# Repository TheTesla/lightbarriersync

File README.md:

# Light Barrier Synchronous

This is a robust continuous wave modulated light barrier with a synchronous detector. The sensitivity is very low against other modulated ligth sources. All electrical interfaces are protected against reverse polarity, over voltage and over current.

It contains only easily available discrete standard components and the board has only one solder side.

## Technical Data

| Parameter              | Min | Typ | Max | Unit |
| ---------------------- | --- | --- | --- | ---- |
| Operating Voltage      | 3.3 | 5   |  35 |    V |
| Current Consumption    |     |     |  10 |   mA |
| Output Sink Current    |     |     | 800 |   uA |
| Temperature Range      | 0   |     |  70 |   °C |
| Carrier Frequency      |     | 7   |     |  kHz |

## Pictures

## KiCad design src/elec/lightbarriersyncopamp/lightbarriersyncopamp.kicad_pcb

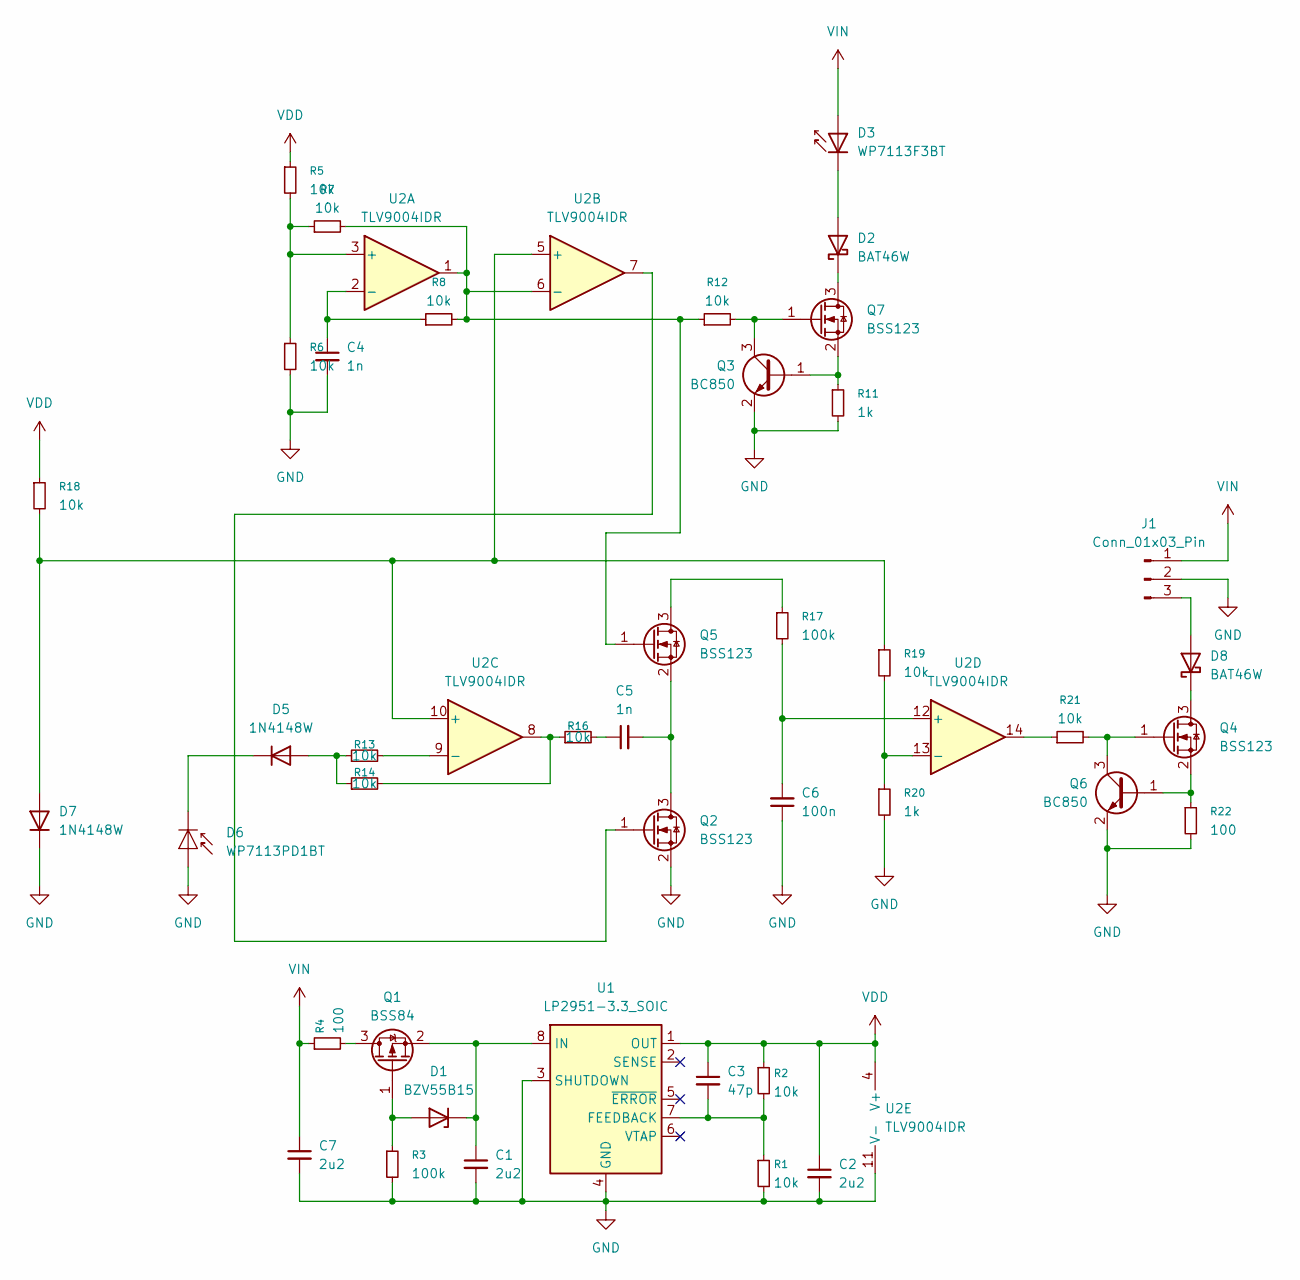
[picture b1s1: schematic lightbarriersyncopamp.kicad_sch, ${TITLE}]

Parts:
C1, C2, C7: 2u2; C_0805_2012Metric
C3: 47p; C_0805_2012Metric
C4, C5: 1n; C_0805_2012Metric
C6: 100n; C_0805_2012Metric
D1: BZV55B15; D_MiniMELF
D2, D8: BAT46W; D_SOD-123
D3: WP7113F3BT; LED_D5.0mm_IRGrey
D5, D7: 1N4148W; D_SOD-123
D6: WP7113PD1BT; LED_D5.0mm_IRGrey
J1: Conn_01x03_Pin; PinHeader_1x03_P2.54mm_Vertical
Q1: BSS84; SOT-23
Q2, Q4, Q5, Q7: BSS123; SOT-23
Q3, Q6: BC850; SOT-23
R1, R2, R5, R6, R7, R8, R12, R13, R14, R16, R18, R19, R21: 10k; R_0805_2012Metric
R3, R17: 100k; R_0805_2012Metric
R4, R22: 100; R_0805_2012Metric
R11, R20: 1k; R_0805_2012Metric
U1: LP2951-3.3_SOIC; SOIC-8_3.9x4.9mm_P1.27mm
U2: TLV9004IDR; SOIC-14_3.9x8.7mm_P1.27mm

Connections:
GND: C1.2, C2.2, C4.2, C6.1, C7.2, D6.2 (A), D7.1 (K), J1.2, Q2.2 (S), Q3.2 (E), Q6.2 (E), R1.2, R3.2, R6.2, R11.2, R20.2, R22.2, U1.3 (SHUTDOWN), U1.4 (GND), U2.11 (V-)
unnamed: C5.1, R16.2
unnamed: D1.2 (A), Q1.1 (G), R3.1
unnamed: C1.1, D1.1 (K), Q1.2 (S), U1.8 (IN)
unnamed: D2.2 (A), D3.1 (K)
unnamed: D2.1 (K), Q7.3 (D)
unnamed: D5.2 (A), R13.1, R14.1
unnamed: D5.1 (K), D6.1 (K)
unnamed: D7.2 (A), R18.2, R19.1, U2.5 (+), U2.10 (+)
unnamed: D8.2 (A), J1.3
unnamed: D8.1 (K), Q4.3 (D)
unnamed: Q1.3 (D), R4.2
unnamed: C5.2, Q2.3 (D), Q5.2 (S)
unnamed: Q2.1 (G), U2.7
unnamed: Q3.1 (B), Q7.2 (S), R11.1
unnamed: Q3.3 (C), Q7.1 (G), R12.2
unnamed: Q4.1 (G), Q6.3 (C), R21.2
unnamed: Q4.2 (S), Q6.1 (B), R22.1
unnamed: Q5.3 (D), R17.1
unnamed: Q5.1 (G), R7.2, R8.2, R12.1, U2.1, U2.6 (-)
unnamed: R14.2, R16.1, U2.8
unnamed: R21.1, U2.14
unnamed: C3.2, R1.1, R2.2, U1.7 (FEEDBACK)
unnamed: R5.2, R6.1, R7.1, U2.3 (+)
unnamed: C4.1, R8.1, U2.2 (-)
unnamed: R13.2, U2.9 (-)
unnamed: C6.2, R17.2, U2.12 (+)
unnamed: R19.2, R20.1, U2.13 (-)
VDD: C2.1, C3.1, R2.1, R5.1, R18.1, U1.1 (OUT), U2.4 (V+)
VIN: C7.1, D3.2 (A), J1.1, R4.1

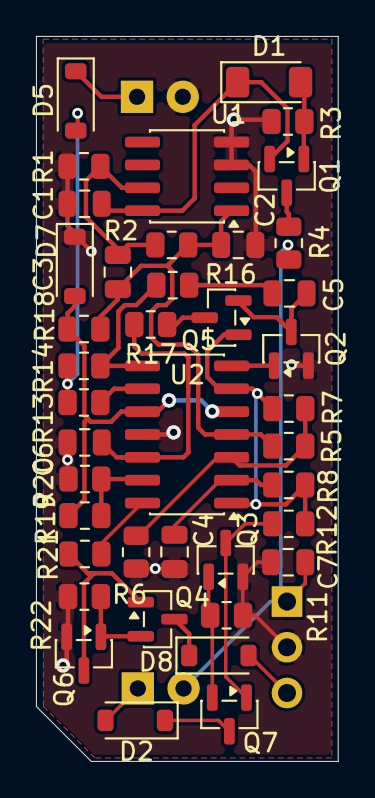
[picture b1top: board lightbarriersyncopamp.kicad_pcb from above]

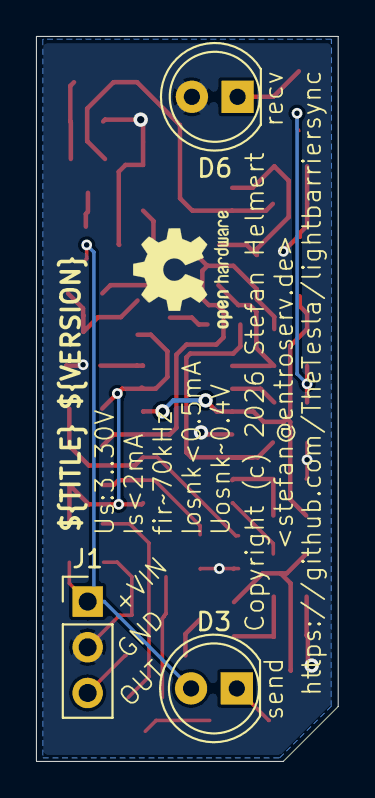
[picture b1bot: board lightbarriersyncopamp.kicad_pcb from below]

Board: 2 copper layers, 16.8 x 40.3 mm, 43 parts (3 on the bottom side), 30 nets.

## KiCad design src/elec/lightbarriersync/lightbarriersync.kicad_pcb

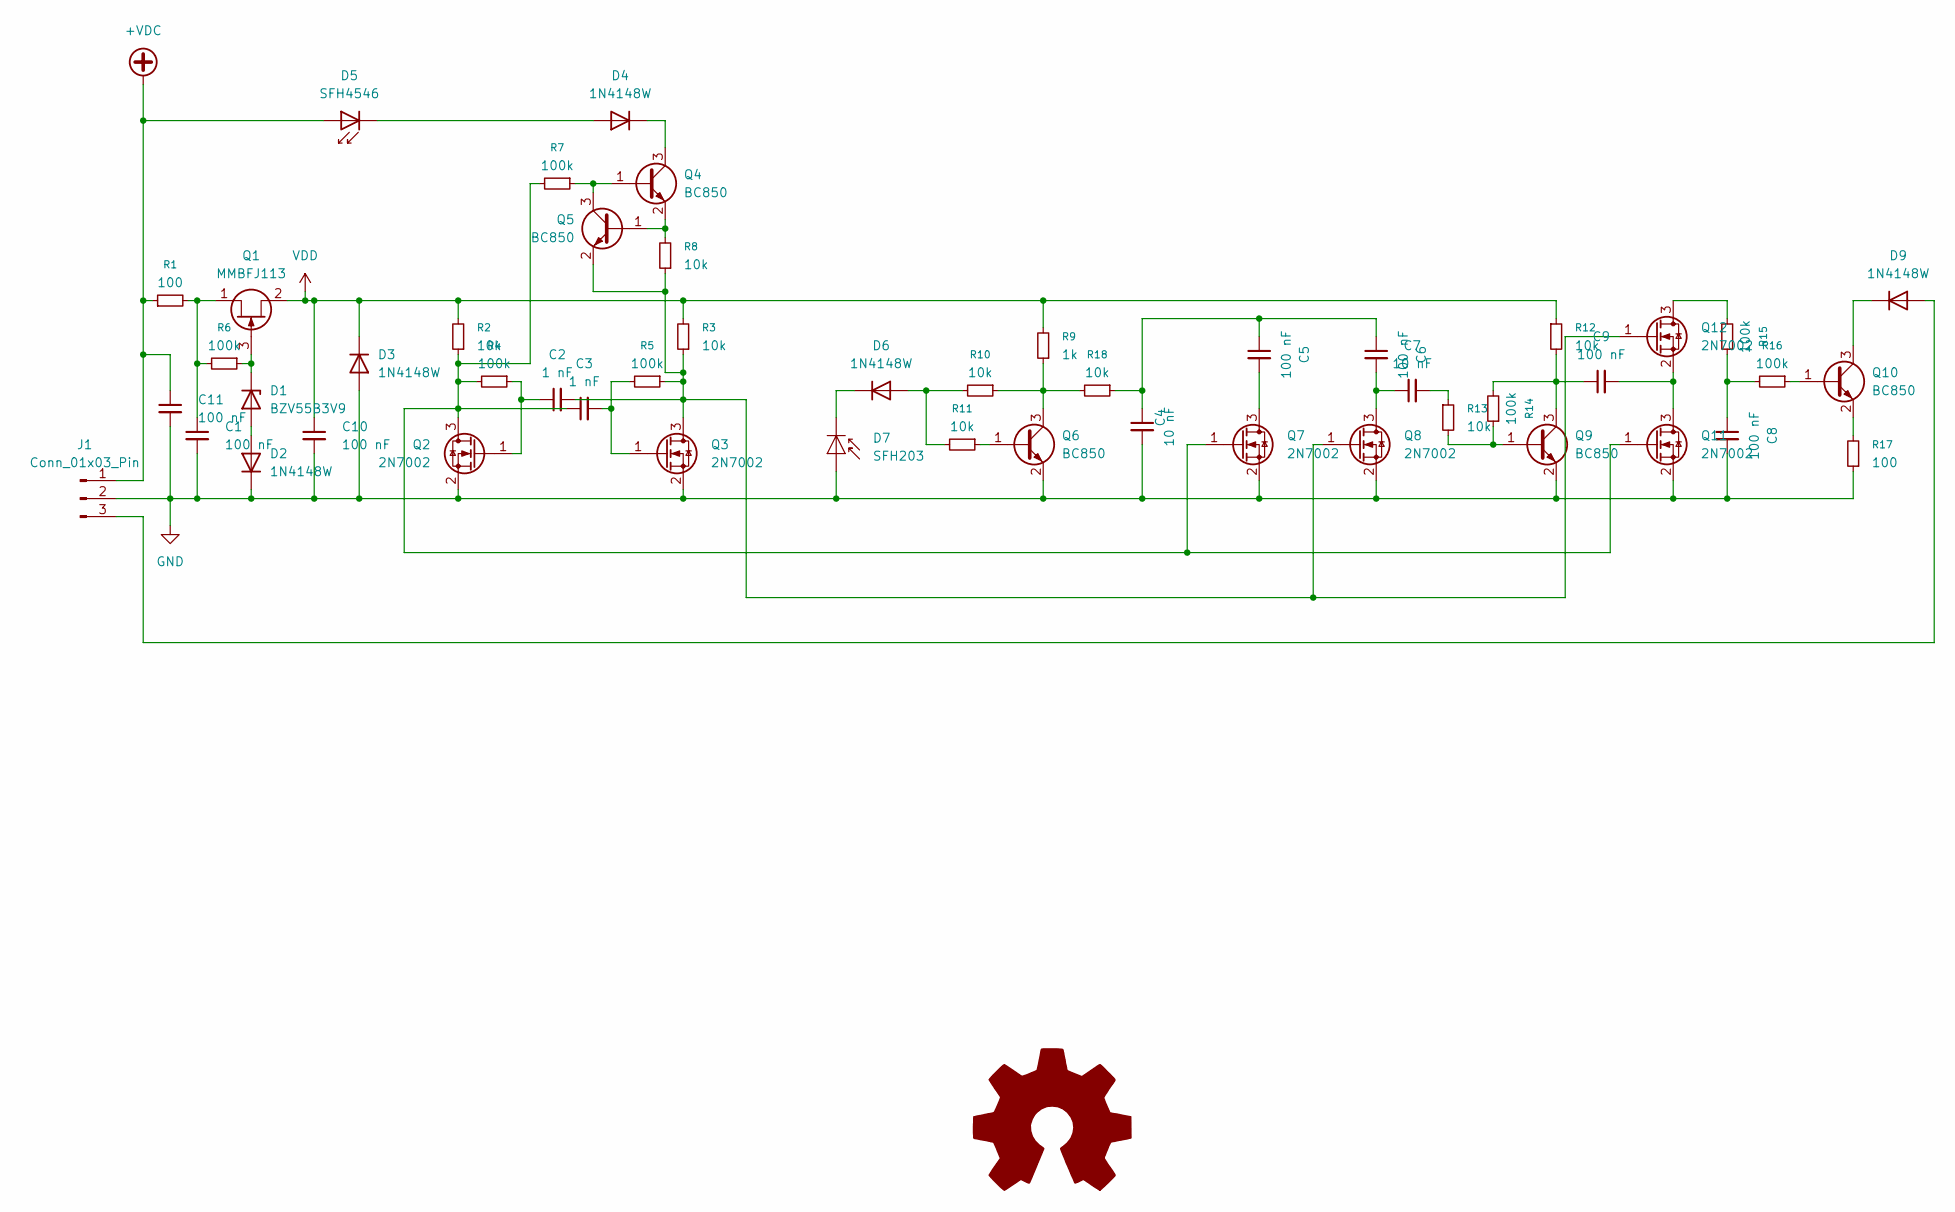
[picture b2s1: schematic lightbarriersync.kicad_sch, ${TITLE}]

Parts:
C1, C5, C6, C8, C9, C10, C11: 100 nF; C_0805_2012Metric
C2, C3: 1 nF; C_0805_2012Metric
C4, C7: 10 nF; C_0805_2012Metric
D1: BZV55B3V9; D_MiniMELF
D2, D3, D4, D6, D9: 1N4148W; D_SOD-123
D5: SFH4546; LED_D5.0mm_IRGrey
D7: SFH203; LED_D5.0mm_IRGrey
J1: Conn_01x03_Pin; PinHeader_1x03_P2.54mm_Vertical
Q1: MMBFJ113; SOT-23
Q2, Q3, Q7, Q8, Q11, Q12: 2N7002; SOT-23
Q4, Q5, Q6, Q9, Q10: BC850; SOT-23
R1, R17: 100; R_0805_2012Metric
R2, R3, R8, R10, R11, R12, R13, R18: 10k; R_0805_2012Metric
R4, R5, R6, R7, R14, R15, R16: 100k; R_0805_2012Metric
R9: 1k; R_0805_2012Metric

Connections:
+VDC: C11.1, D5.2 (A), J1.1, R1.1
GND: C1.2, C4.2, C8.2, C10.2, C11.2, D2.1 (K), D3.2 (A), D7.2 (A), J1.2, Q2.2 (S), Q3.2 (S), Q6.2 (E), Q7.2 (S), Q8.2 (S), Q9.2 (E), Q11.2 (S), R17.1
unnamed: C4.1, C5.1, C6.1, R18.1
unnamed: C7.2, R13.1
unnamed: C8.1, R15.1, R16.2
unnamed: D1.2 (A), D2.2 (A)
unnamed: D1.1 (K), Q1.3 (G), R6.1
unnamed: D4.2 (A), D5.1 (K)
unnamed: D4.1 (K), Q4.3 (C)
unnamed: D6.2 (A), R10.2, R11.2
unnamed: D6.1 (K), D7.1 (K)
unnamed: D9.2 (A), J1.3
unnamed: D9.1 (K), Q10.3 (C)
unnamed: C1.1, Q1.1 (D), R1.2, R6.2
unnamed: C2.1, Q2.1 (G), R4.1
unnamed: C3.2, Q3.1 (G), R5.2
unnamed: Q4.1 (B), Q5.3 (C), R7.1
unnamed: Q4.2 (E), Q5.1 (B), R8.2
unnamed: Q6.1 (B), R11.1
unnamed: Q6.3 (C), R9.1, R10.1, R18.2
unnamed: C5.2, Q7.3 (D)
unnamed: C6.2, C7.1, Q8.3 (D)
unnamed: Q9.1 (B), R13.2, R14.1
unnamed: C9.1, Q9.3 (C), R12.2, R14.2
unnamed: Q10.1 (B), R16.1
unnamed: Q10.2 (E), R17.2
unnamed: C9.2, Q11.3 (D), Q12.2 (S)
unnamed: C3.1, Q2.3 (D), Q7.1 (G), Q11.1 (G), R2.1, R4.2, R7.2
unnamed: Q12.3 (D), R15.2
unnamed: C2.2, Q3.3 (D), Q5.2 (E), Q8.1 (G), Q12.1 (G), R3.1, R5.1, R8.1
VDD: C10.1, D3.1 (K), Q1.2 (S), R2.2, R3.2, R9.2, R12.1

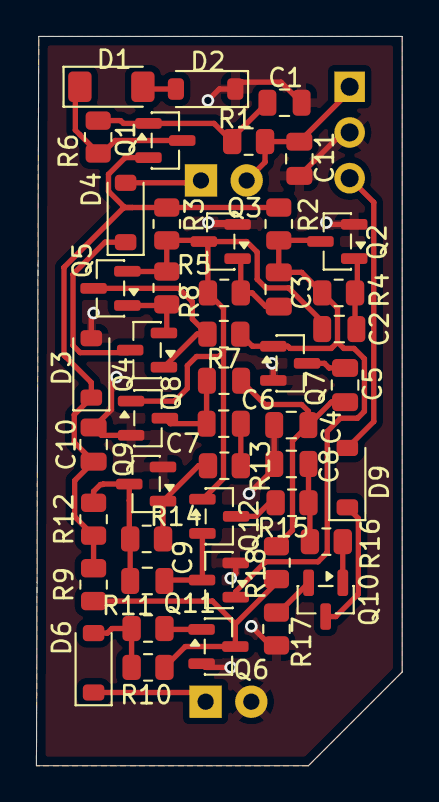
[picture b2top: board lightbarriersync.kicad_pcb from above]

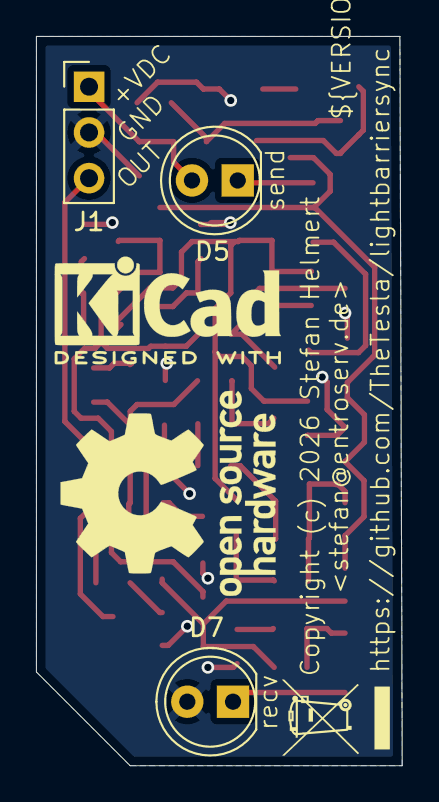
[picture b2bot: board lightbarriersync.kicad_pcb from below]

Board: 2 copper layers, 20.3 x 40.5 mm, 50 parts (3 on the bottom side), 31 nets.

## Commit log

2026-04-18 PCB nearly ready
2026-04-18 board ready
2026-04-18 added simulation file, .gitignore
2026-04-18 License, Readme
2026-05-17 opamp version
2026-05-17 restored
2026-05-17 addec copyright; ToDo: variables, version, opamp variant note, data on silkscreen
2026-05-20 ready to build
2026-05-20 minor reference label movement
2026-05-26 version 0.2 optimized with less components
2026-05-26 shifted text

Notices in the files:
src/elec/lightbarriersync/lightbarriersync.kicad_pcb:
Copyright (c) 2026 Stefan Helmert
